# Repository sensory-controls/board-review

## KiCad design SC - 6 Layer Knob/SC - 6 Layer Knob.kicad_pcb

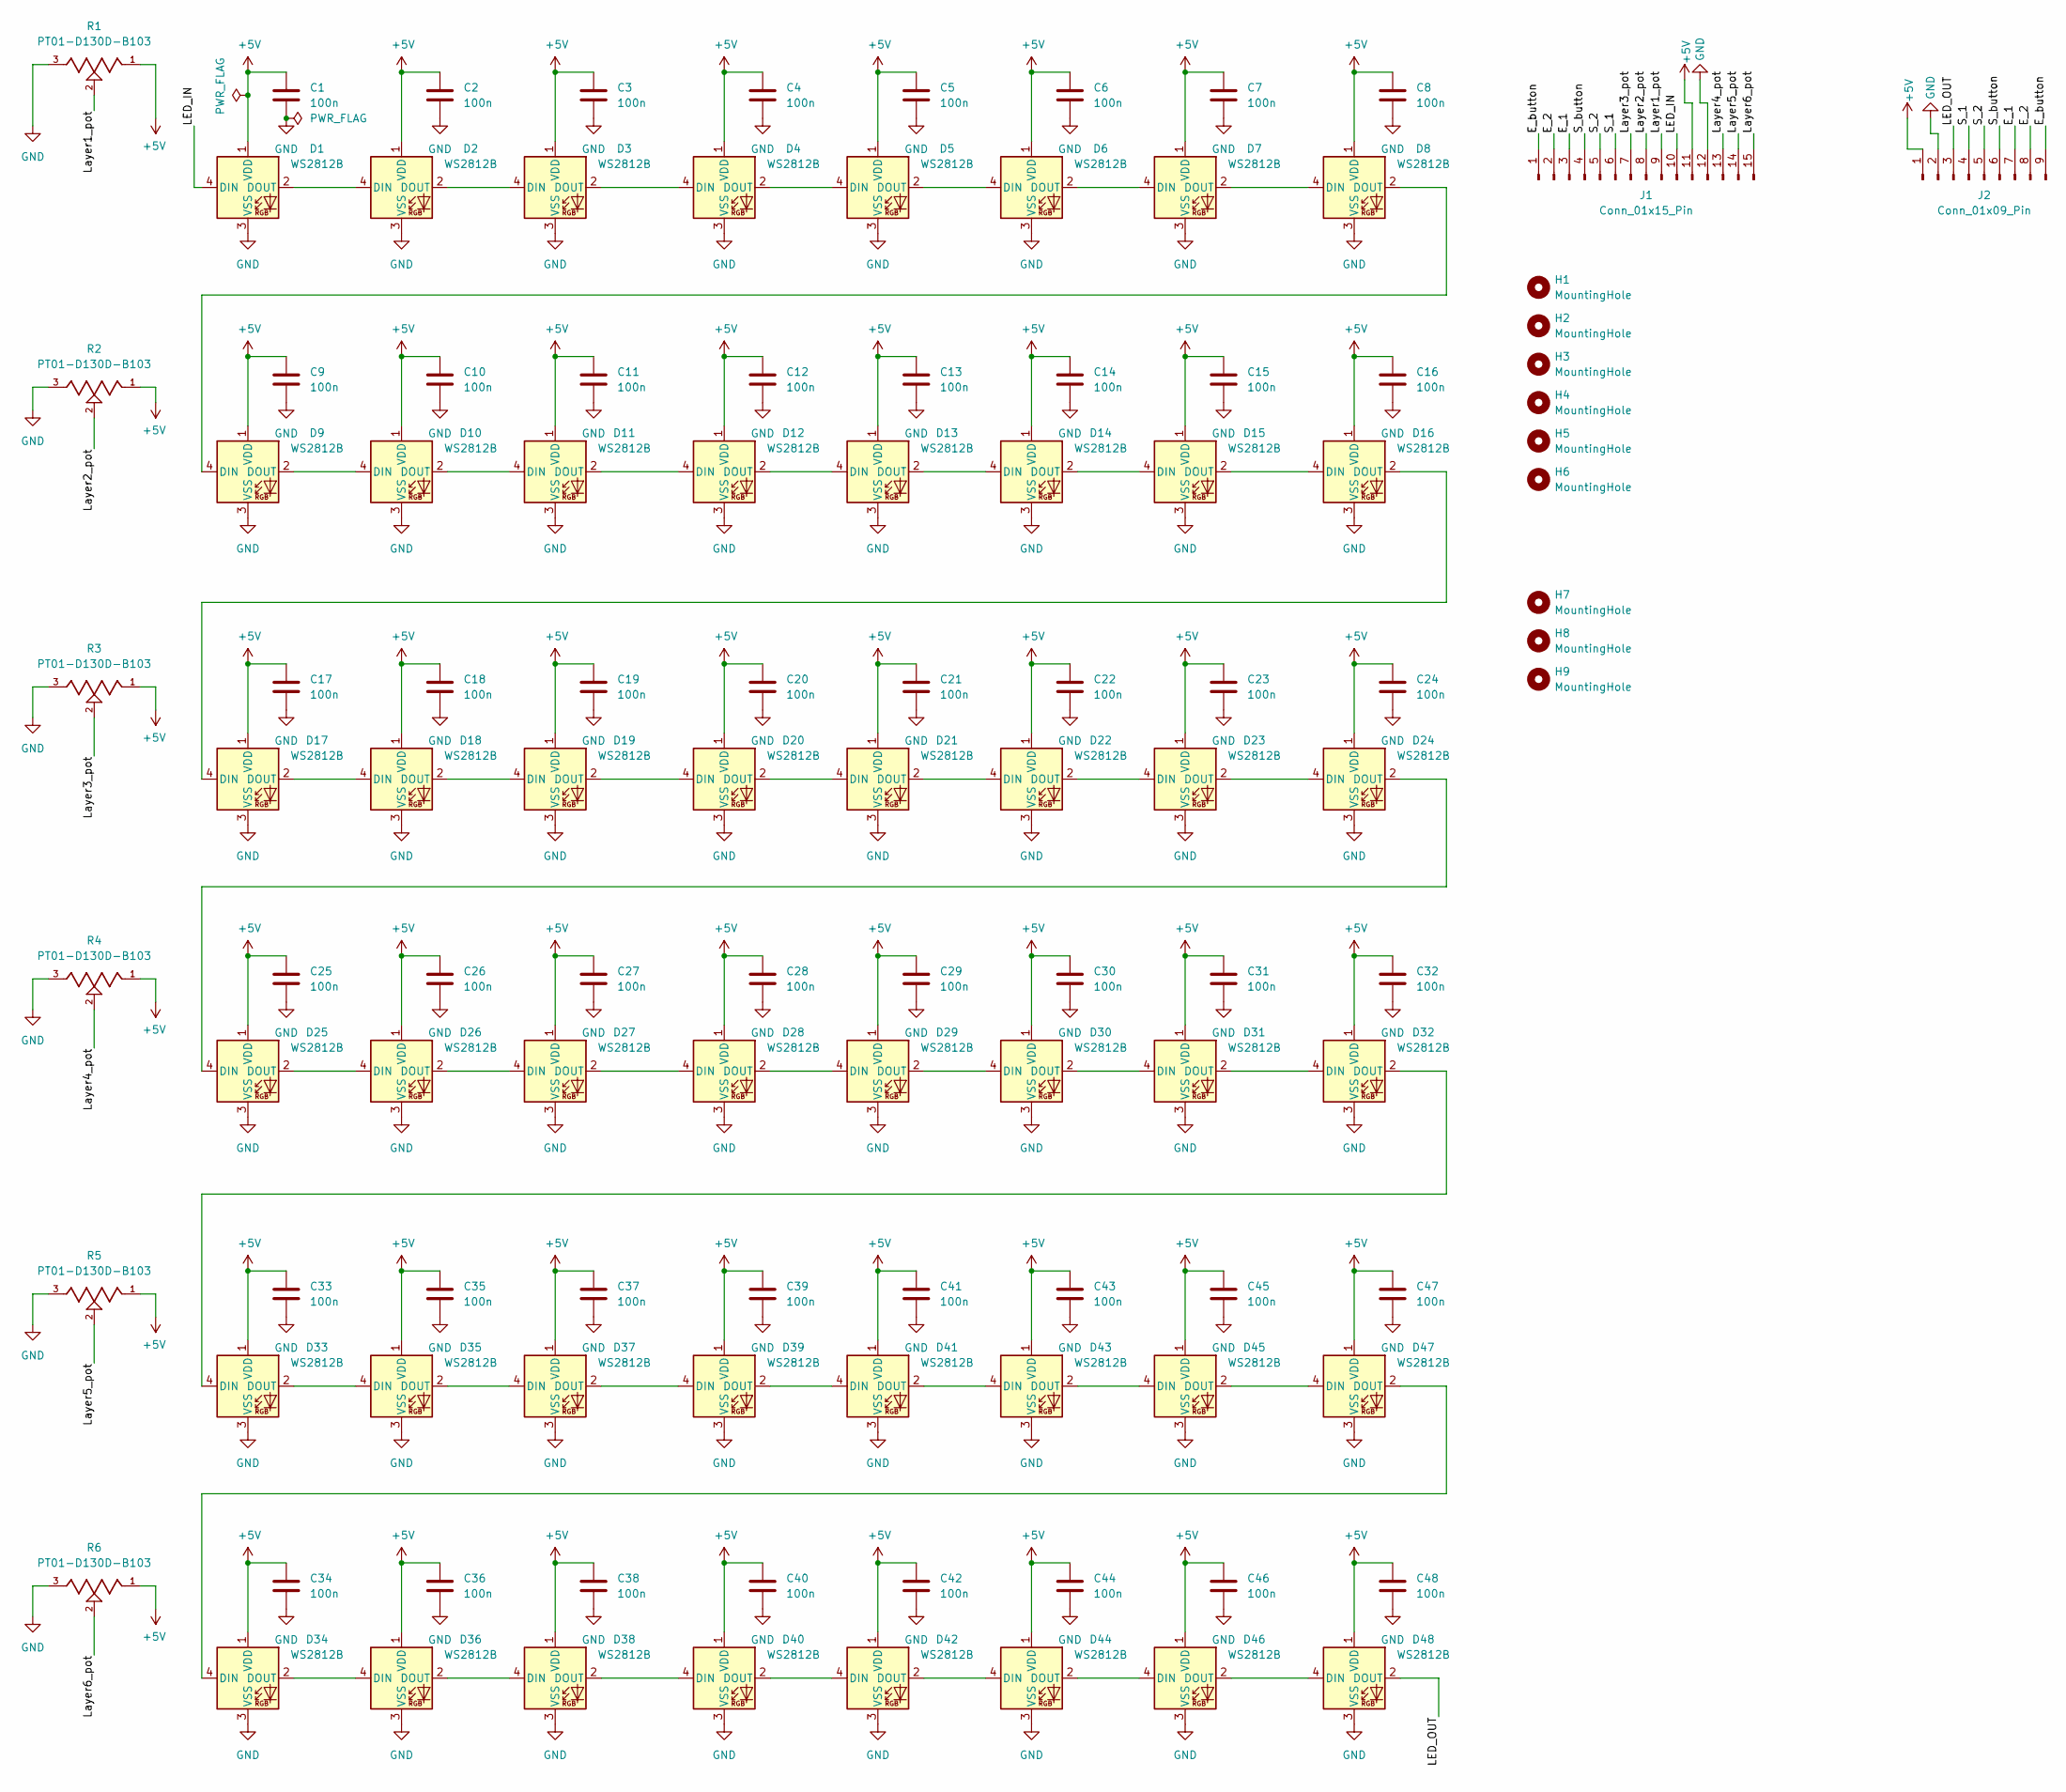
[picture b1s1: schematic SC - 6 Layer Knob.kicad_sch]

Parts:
C1, C2, C3, C4, C5, C6, C7, C8, C9, C10, C11, C12, C13, C14, C15, C16, C17, C18, C19, C20, C21, C22, C23, C24, C25, C26, C27, C28, C29, C30, C31, C32, C33, C34, C35, C36, C37, C38, C39, C40, C41, C42, C43, C44, C45, C46, C47, C48: 100n; C_0402_1005Metric
D1, D2, D3, D4, D5, D6, D7, D8, D9, D10, D11, D12, D13, D14, D15, D16, D17, D18, D19, D20, D21, D22, D23, D24, D25, D26, D27, D28, D29, D30, D31, D32, D33, D34, D35, D36, D37, D38, D39, D40, D41, D42, D43, D44, D45, D46, D47, D48: WS2812B; LED_WS2812B_PLCC4_5.0x5.0mm_P3.2mm
H1, H2, H3, H5: MountingHole; MountingHole_3.5mm
H4, H6: MountingHole; MountingHole_3.2mm_M3_Pad
H7, H8, H9: MountingHole; ToolingHole_1.152mm
J1: Conn_01x15_Pin; JST_PH_S15B-PH-K_1x15_P2.00mm_Horizontal
J2: Conn_01x09_Pin; JST_PH_S9B-PH-K_1x09_P2.00mm_Horizontal
R1, R2, R3, R4, R5, R6: PT01-D130D-B103; TRIM_PT01-D130D-B103; PARTREV 1.0

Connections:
+5V: C1.1, C2.1, C3.1, C4.1, C5.1, C6.1, C7.1, C8.1, C9.1, C10.1, C11.1, C12.1, C13.1, C14.1, C15.1, C16.1, C17.1, C18.1, C19.1, C20.1, C21.1, C22.1, C23.1, C24.1, C25.1, C26.1, C27.1, C28.1, C29.1, C30.1, C31.1, C32.1, C33.1, C34.1, C35.1, C36.1, C37.1, C38.1, C39.1, C40.1, C41.1, C42.1, C43.1, C44.1, C45.1, C46.1, C47.1, C48.1, D1.1 (VDD), D2.1 (VDD), D3.1 (VDD), D4.1 (VDD), D5.1 (VDD), D6.1 (VDD), D7.1 (VDD), D8.1 (VDD), D9.1 (VDD), D10.1 (VDD), D11.1 (VDD), D12.1 (VDD), D13.1 (VDD), D14.1 (VDD), D15.1 (VDD), D16.1 (VDD), D17.1 (VDD), D18.1 (VDD), D19.1 (VDD), D20.1 (VDD), D21.1 (VDD), D22.1 (VDD), D23.1 (VDD), D24.1 (VDD), D25.1 (VDD), D26.1 (VDD), D27.1 (VDD), D28.1 (VDD), D29.1 (VDD), D30.1 (VDD), D31.1 (VDD), D32.1 (VDD), D33.1 (VDD), D34.1 (VDD), D35.1 (VDD), D36.1 (VDD), D37.1 (VDD), D38.1 (VDD), D39.1 (VDD), D40.1 (VDD), D41.1 (VDD), D42.1 (VDD), D43.1 (VDD), D44.1 (VDD), D45.1 (VDD), D46.1 (VDD), D47.1 (VDD), D48.1 (VDD), J1.11, J2.1, R1.1, R2.1, R3.1, R4.1, R5.1, R6.1
/E_1: J1.3, J2.7
/E_2: J1.2, J2.8
/E_button: J1.1, J2.9
/LED_IN: D1.4 (DIN), J1.10
/LED_OUT: D48.2 (DOUT), J2.3
/Layer1_pot: J1.9, R1.2
/Layer2_pot: J1.8, R2.2
/Layer3_pot: J1.7, R3.2
/Layer4_pot: J1.13, R4.2
/Layer5_pot: J1.14, R5.2
/Layer6_pot: J1.15, R6.2
/S_1: J1.6, J2.4
/S_2: J1.5, J2.5
/S_button: J1.4, J2.6
GND: C1.2, C2.2, C3.2, C4.2, C5.2, C6.2, C7.2, C8.2, C9.2, C10.2, C11.2, C12.2, C13.2, C14.2, C15.2, C16.2, C17.2, C18.2, C19.2, C20.2, C21.2, C22.2, C23.2, C24.2, C25.2, C26.2, C27.2, C28.2, C29.2, C30.2, C31.2, C32.2, C33.2, C34.2, C35.2, C36.2, C37.2, C38.2, C39.2, C40.2, C41.2, C42.2, C43.2, C44.2, C45.2, C46.2, C47.2, C48.2, D1.3 (VSS), D2.3 (VSS), D3.3 (VSS), D4.3 (VSS), D5.3 (VSS), D6.3 (VSS), D7.3 (VSS), D8.3 (VSS), D9.3 (VSS), D10.3 (VSS), D11.3 (VSS), D12.3 (VSS), D13.3 (VSS), D14.3 (VSS), D15.3 (VSS), D16.3 (VSS), D17.3 (VSS), D18.3 (VSS), D19.3 (VSS), D20.3 (VSS), D21.3 (VSS), D22.3 (VSS), D23.3 (VSS), D24.3 (VSS), D25.3 (VSS), D26.3 (VSS), D27.3 (VSS), D28.3 (VSS), D29.3 (VSS), D30.3 (VSS), D31.3 (VSS), D32.3 (VSS), D33.3 (VSS), D34.3 (VSS), D35.3 (VSS), D36.3 (VSS), D37.3 (VSS), D38.3 (VSS), D39.3 (VSS), D40.3 (VSS), D41.3 (VSS), D42.3 (VSS), D43.3 (VSS), D44.3 (VSS), D45.3 (VSS), D46.3 (VSS), D47.3 (VSS), D48.3 (VSS), J1.12, J2.2, R1.3, R2.3, R3.3, R4.3, R5.3, R6.3
unnamed: D1.2 (DOUT), D2.4 (DIN)
unnamed: D2.2 (DOUT), D3.4 (DIN)
unnamed: D3.2 (DOUT), D4.4 (DIN)
unnamed: D4.2 (DOUT), D5.4 (DIN)
unnamed: D5.2 (DOUT), D6.4 (DIN)
unnamed: D6.2 (DOUT), D7.4 (DIN)
unnamed: D7.2 (DOUT), D8.4 (DIN)
unnamed: D8.2 (DOUT), D9.4 (DIN)
unnamed: D9.2 (DOUT), D10.4 (DIN)
unnamed: D10.2 (DOUT), D11.4 (DIN)
unnamed: D11.2 (DOUT), D12.4 (DIN)
unnamed: D12.2 (DOUT), D13.4 (DIN)
unnamed: D13.2 (DOUT), D14.4 (DIN)
unnamed: D14.2 (DOUT), D15.4 (DIN)
unnamed: D15.2 (DOUT), D16.4 (DIN)
unnamed: D16.2 (DOUT), D17.4 (DIN)
unnamed: D17.2 (DOUT), D18.4 (DIN)
unnamed: D18.2 (DOUT), D19.4 (DIN)
unnamed: D19.2 (DOUT), D20.4 (DIN)
unnamed: D20.2 (DOUT), D21.4 (DIN)
unnamed: D21.2 (DOUT), D22.4 (DIN)
unnamed: D22.2 (DOUT), D23.4 (DIN)
unnamed: D23.2 (DOUT), D24.4 (DIN)
unnamed: D24.2 (DOUT), D25.4 (DIN)
unnamed: D25.2 (DOUT), D26.4 (DIN)
unnamed: D26.2 (DOUT), D27.4 (DIN)
unnamed: D27.2 (DOUT), D28.4 (DIN)
unnamed: D28.2 (DOUT), D29.4 (DIN)
unnamed: D29.2 (DOUT), D30.4 (DIN)
unnamed: D30.2 (DOUT), D31.4 (DIN)
unnamed: D31.2 (DOUT), D32.4 (DIN)
unnamed: D32.2 (DOUT), D33.4 (DIN)
unnamed: D33.2 (DOUT), D35.4 (DIN)
unnamed: D34.4 (DIN), D47.2 (DOUT)
unnamed: D34.2 (DOUT), D36.4 (DIN)
unnamed: D35.2 (DOUT), D37.4 (DIN)
unnamed: D36.2 (DOUT), D38.4 (DIN)
unnamed: D37.2 (DOUT), D39.4 (DIN)
unnamed: D38.2 (DOUT), D40.4 (DIN)
unnamed: D39.2 (DOUT), D41.4 (DIN)
unnamed: D40.2 (DOUT), D42.4 (DIN)
unnamed: D41.2 (DOUT), D43.4 (DIN)
unnamed: D42.2 (DOUT), D44.4 (DIN)
unnamed: D43.2 (DOUT), D45.4 (DIN)
unnamed: D44.2 (DOUT), D46.4 (DIN)
unnamed: D45.2 (DOUT), D47.4 (DIN)
unnamed: D46.2 (DOUT), D48.4 (DIN)

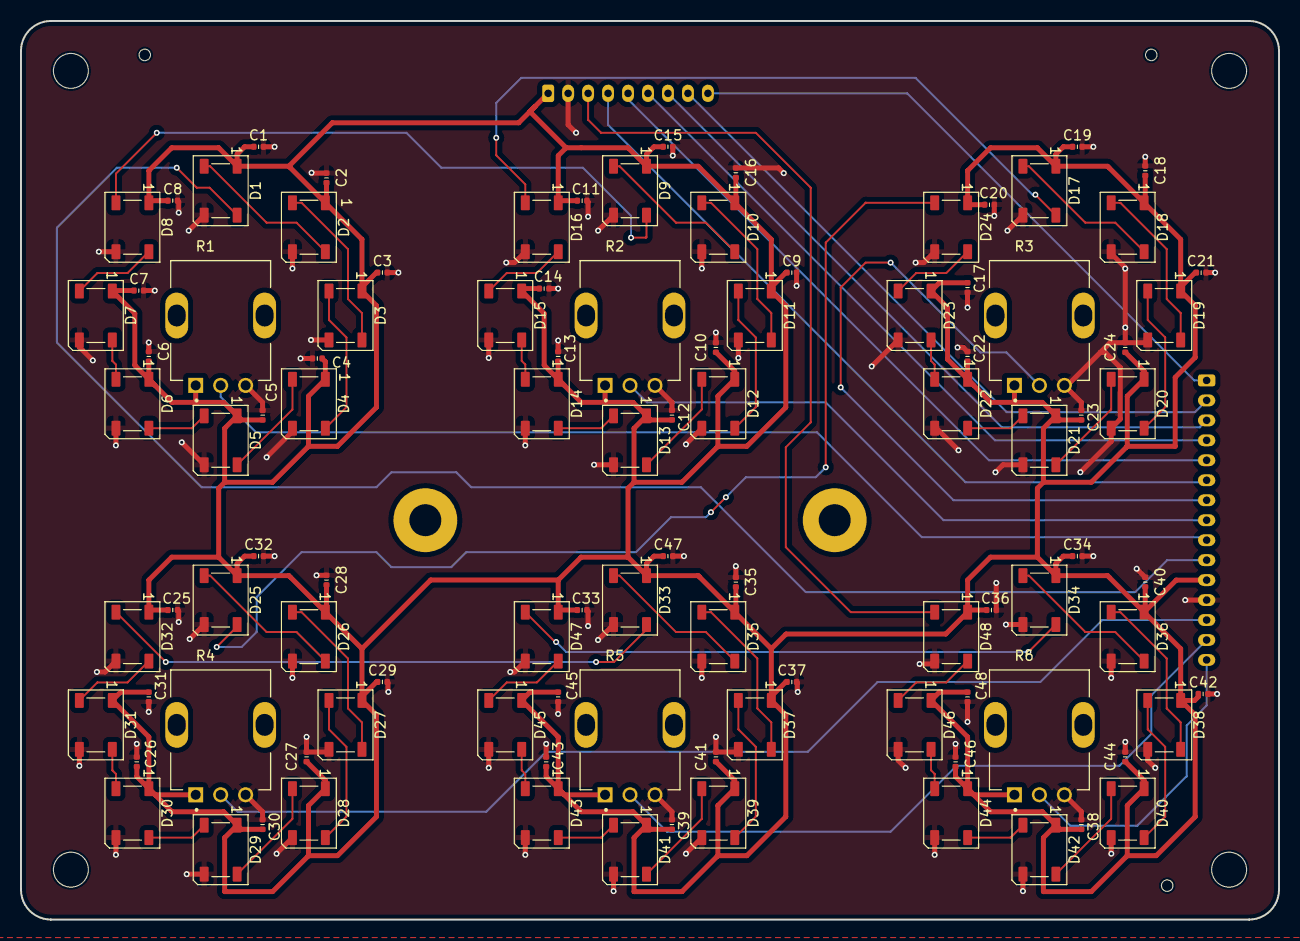
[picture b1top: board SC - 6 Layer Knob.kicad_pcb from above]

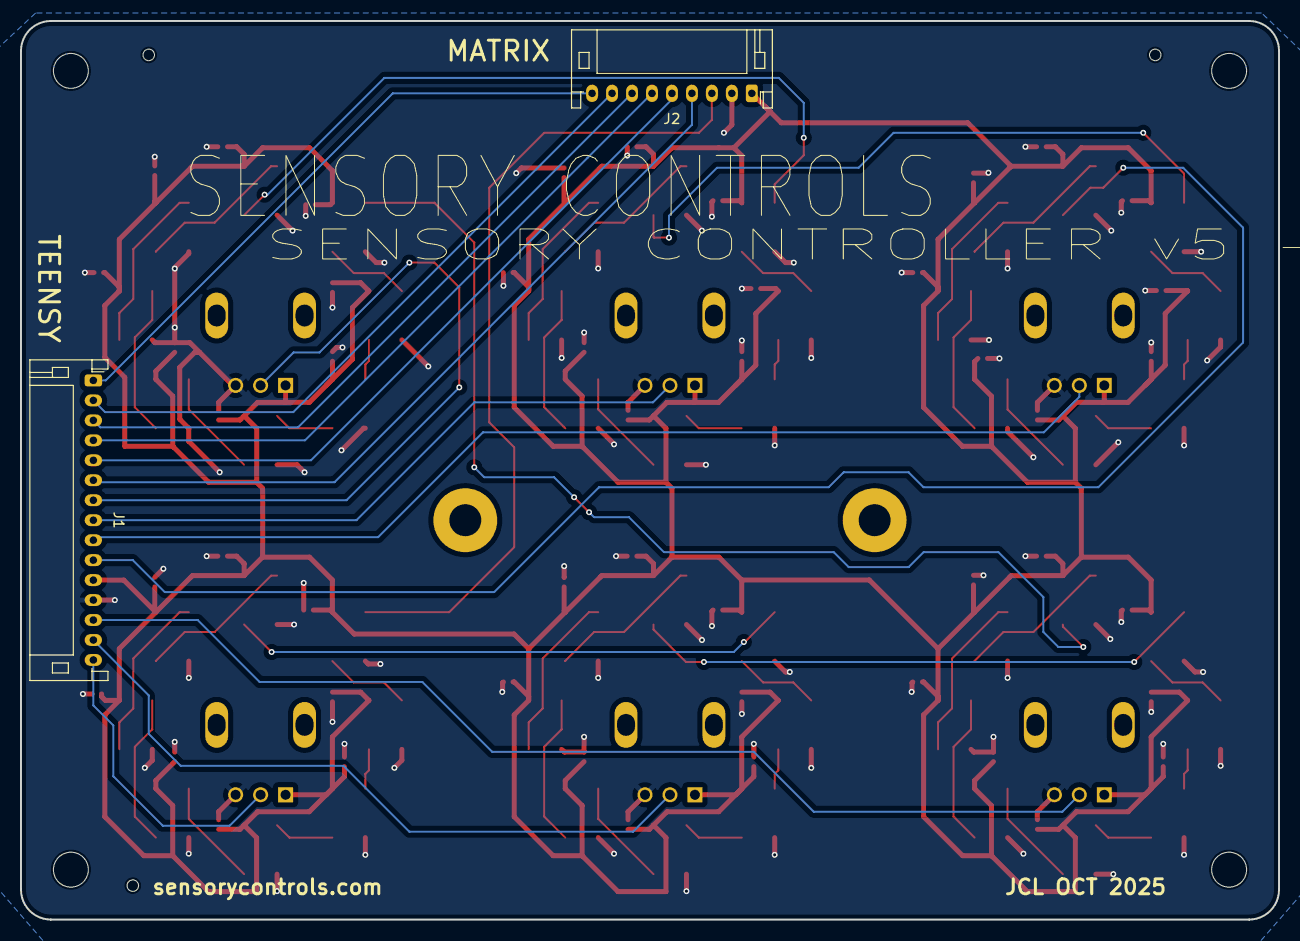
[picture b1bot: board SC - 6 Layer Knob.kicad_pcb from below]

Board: 2 copper layers, 126.0 x 90.0 mm, 113 parts (2 on the bottom side), 63 nets.

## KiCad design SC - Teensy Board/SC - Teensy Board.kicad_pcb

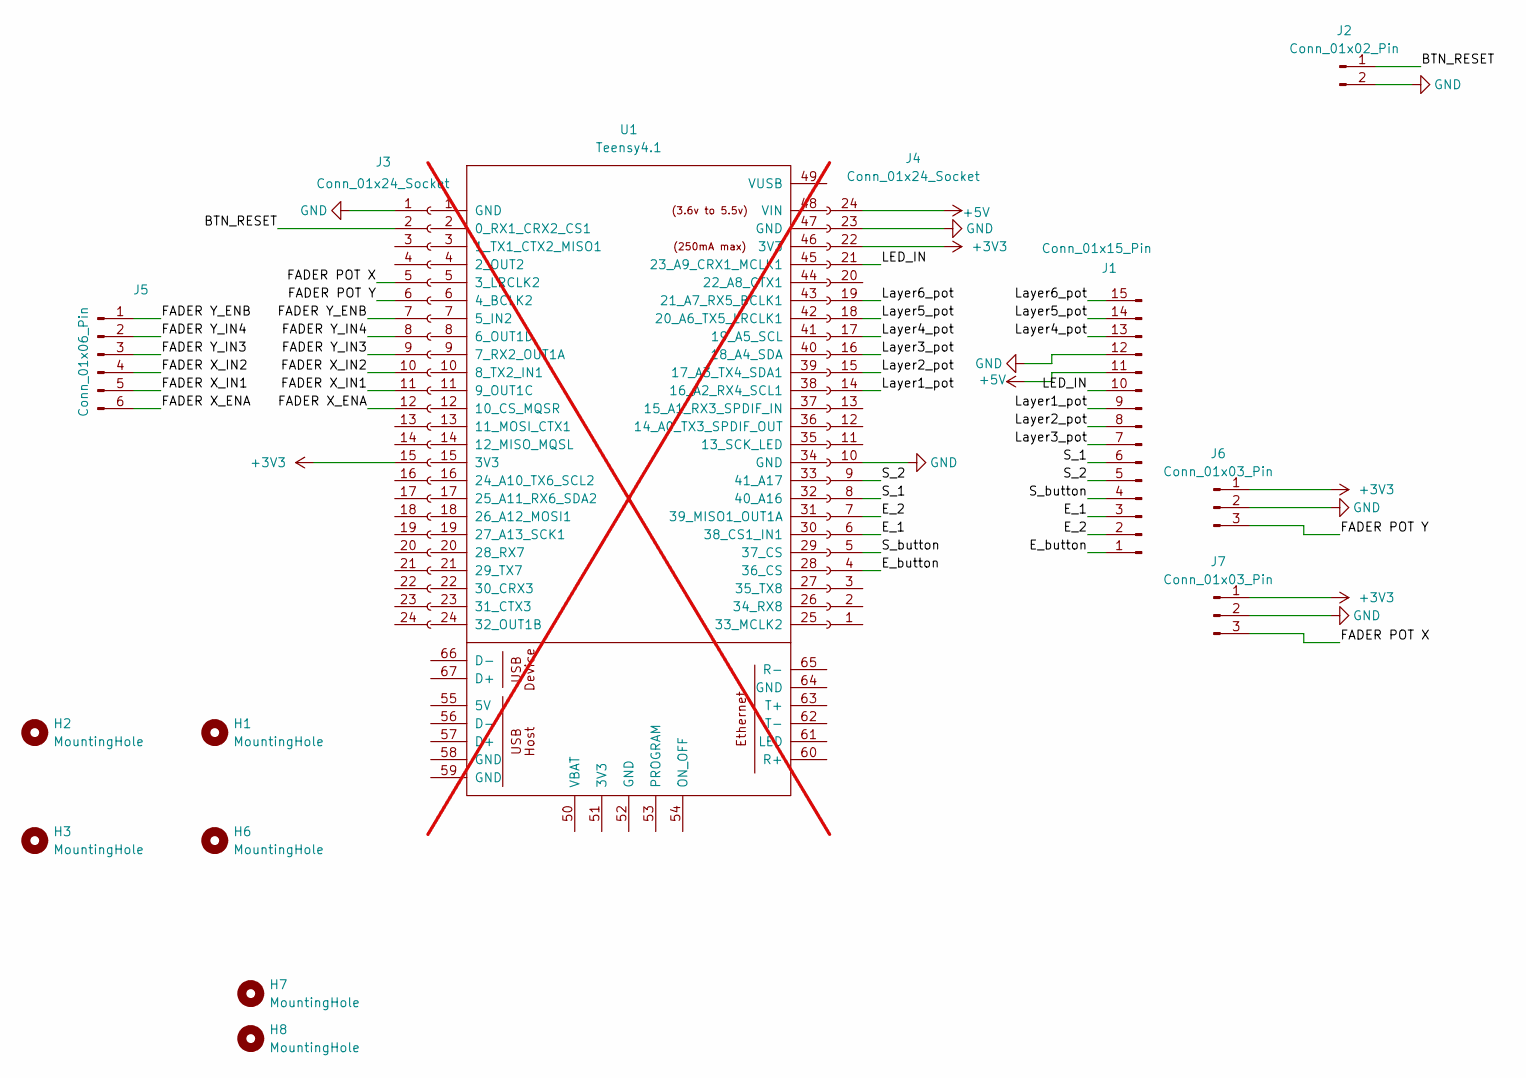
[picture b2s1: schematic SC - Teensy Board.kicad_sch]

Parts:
H1, H2, H3, H6: MountingHole; MountingHole_3.2mm_M3_Pad
H7, H8: MountingHole; ToolingHole_1.152mm
J1: Conn_01x15_Pin; JST_PH_S15B-PH-K_1x15_P2.00mm_Horizontal
J2: Conn_01x02_Pin; JST_PH_S2B-PH-K_1x02_P2.00mm_Horizontal
J3, J4: Conn_01x24_Socket; PinSocket_1x24_P2.54mm_Vertical
J5: Conn_01x06_Pin; JST_PH_S6B-PH-K_1x06_P2.00mm_Horizontal
J6, J7: Conn_01x03_Pin; JST_PH_S3B-PH-K_1x03_P2.00mm_Horizontal
U1: Teensy4.1; Teensy41; not fitted

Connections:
+3V3: J3.15, J4.22, J6.1, J7.1
+5V: J1.11, J4.24
/BTN_RESET: J2.1, J3.2
/E_1: J1.3, J4.6
/E_2: J1.2, J4.7
/E_button: J1.1, J4.4
/FADER POT X: J3.5, J7.3
/FADER POT Y: J3.6, J6.3
/FADER X_ENA: J3.12, J5.6
/FADER X_IN1: J3.11, J5.5
/FADER X_IN2: J3.10, J5.4
/FADER Y_ENB: J3.7, J5.1
/FADER Y_IN3: J3.9, J5.3
/FADER Y_IN4: J3.8, J5.2
/LED_IN: J1.10, J4.21
/Layer1_pot: J1.9, J4.14
/Layer2_pot: J1.8, J4.15
/Layer3_pot: J1.7, J4.16
/Layer4_pot: J1.13, J4.17
/Layer5_pot: J1.14, J4.18
/Layer6_pot: J1.15, J4.19
/S_1: J1.6, J4.8
/S_2: J1.5, J4.9
/S_button: J1.4, J4.5
GND: J1.12, J2.2, J3.1, J4.10, J4.23, J6.2, J7.2

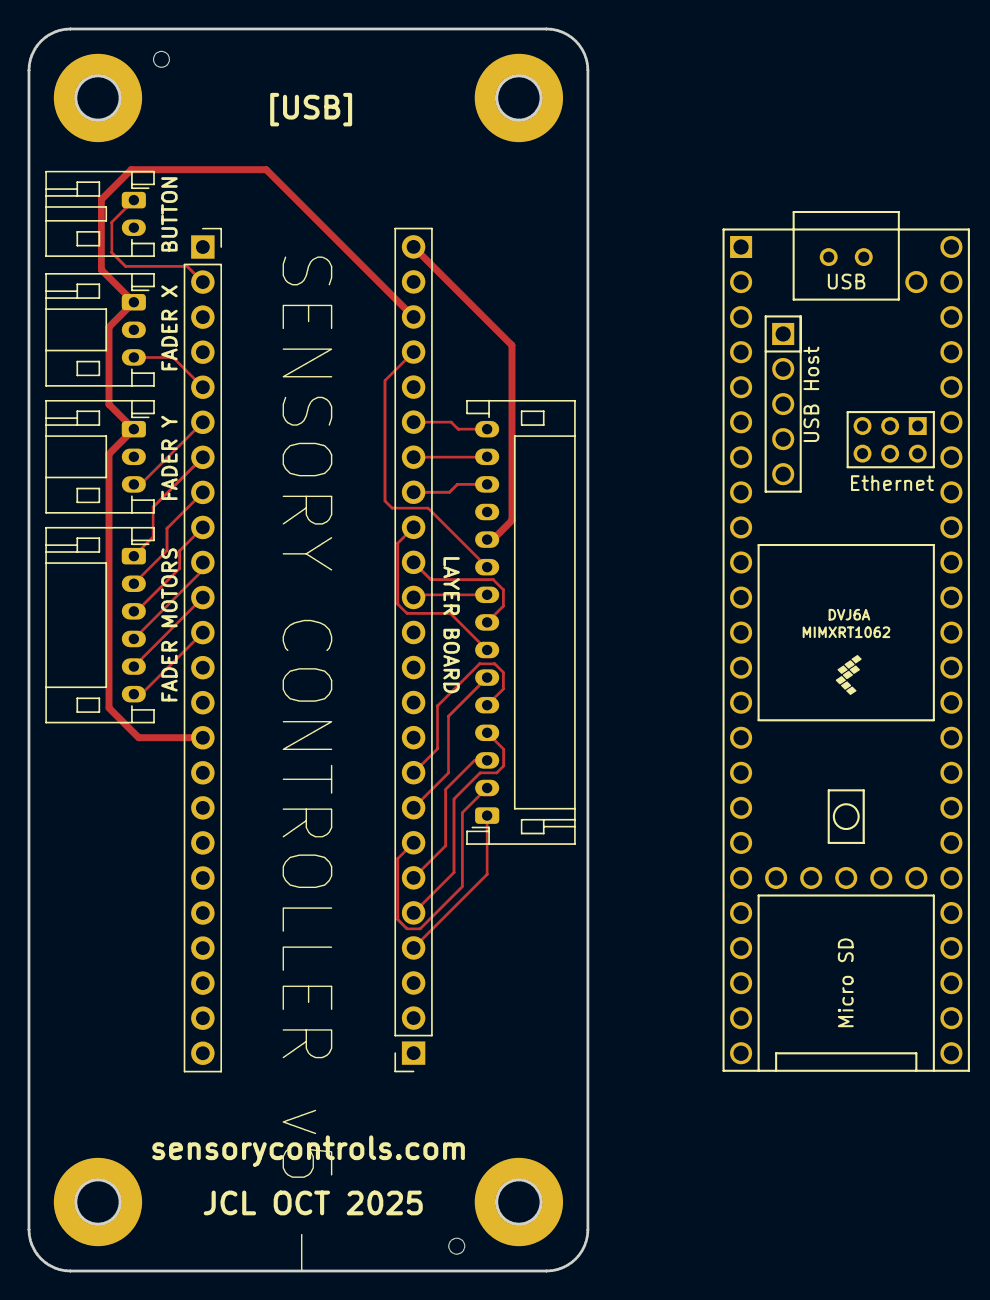
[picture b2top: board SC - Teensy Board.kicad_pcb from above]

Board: 2 copper layers, 40.5 x 90.0 mm, 14 parts (0 on the bottom side), 25 nets.

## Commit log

2025-11-14 review the boards
2025-11-14 rename
2025-11-14 try again
2025-11-14 undo try again :(
2025-11-14 updated after first CL DR
2025-11-14 moved to fit sheet bounds
